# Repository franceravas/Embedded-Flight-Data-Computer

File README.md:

# README.md

Collect inertial and GPS data, timestamp it, and save it to a microSD card for later analysis.

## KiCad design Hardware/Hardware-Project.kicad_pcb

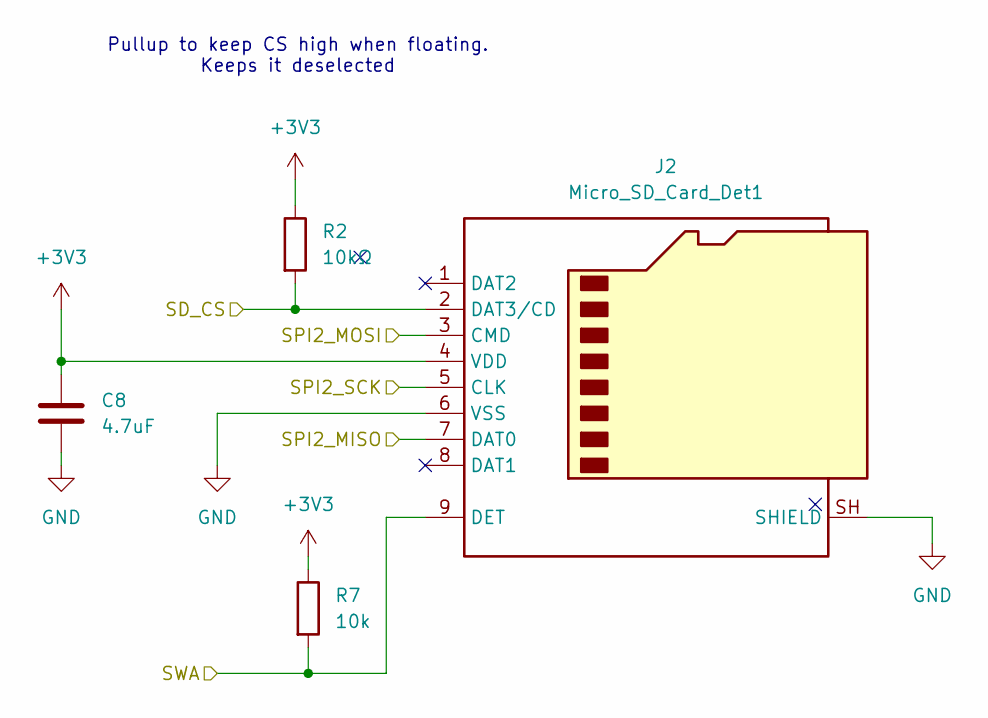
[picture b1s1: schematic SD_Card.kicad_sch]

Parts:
C8: 4.7uF; C_1206_3216Metric_Pad1.33x1.80mm_HandSolder
J2: Micro_SD_Card_Det1; microSD_HC_Hirose_DM3AT-SF-PEJM5
R2: 10kΩ; R_1206_3216Metric_Pad1.30x1.75mm_HandSolder
R7: 10k; R_1206_3216Metric_Pad1.30x1.75mm_HandSolder

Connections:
+3V3: C8.1, J2.4 (VDD), R2.1, R7.1; also elsewhere on the board
/SD_Card/SD_CS: J2.2 (DAT3/CD), R2.2; also elsewhere on the board
/SD_Card/SPI2_MISO: J2.7 (DAT0); also elsewhere on the board
/SD_Card/SPI2_MOSI: J2.3 (CMD); also elsewhere on the board
/SD_Card/SPI2_SCK: J2.5 (CLK); also elsewhere on the board
/SD_Card/SWA: J2.9 (DET), R7.2; also elsewhere on the board
GND: C8.2, J2.6 (VSS), J2.SH (SHIELD); also elsewhere on the board

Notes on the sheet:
Pullup to keep CS high when floating. Keeps it deselected

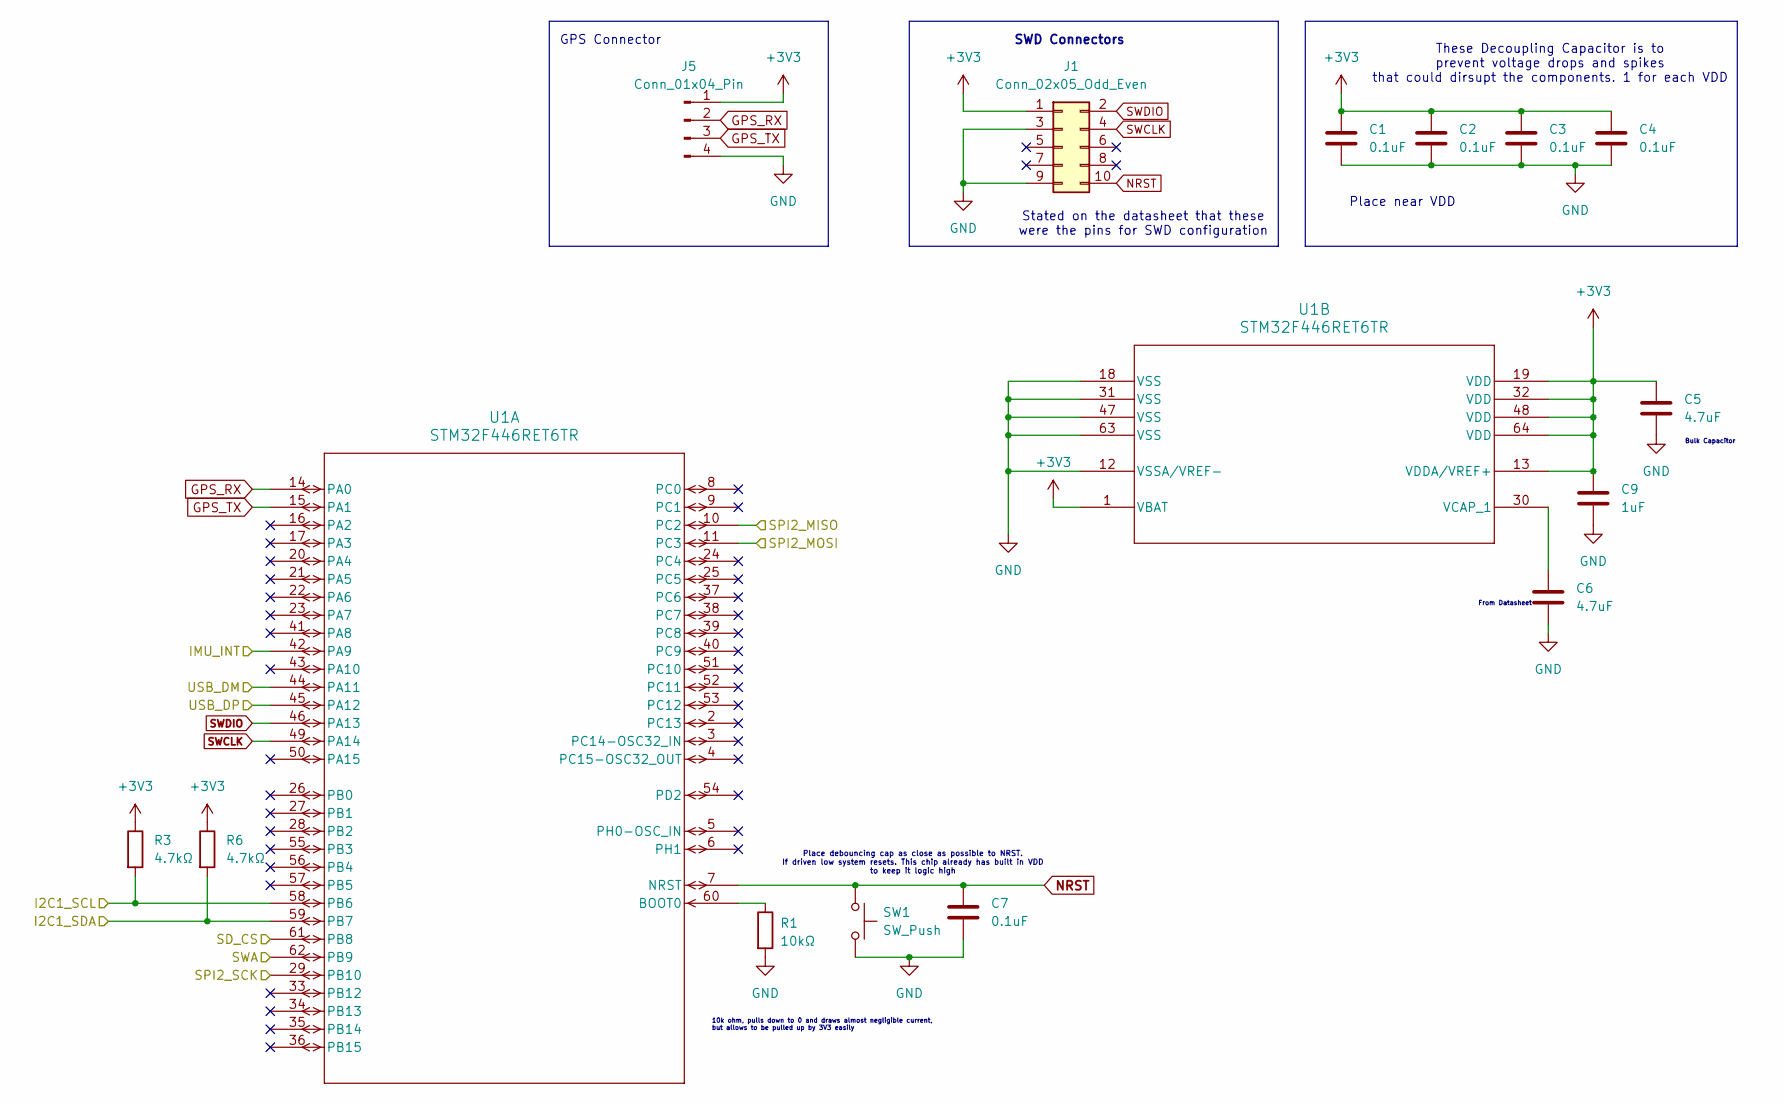
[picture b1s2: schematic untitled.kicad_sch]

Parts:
C1, C2, C3, C4, C7: 0.1uF; C_0603_1608Metric_Pad1.08x0.95mm_HandSolder
C5, C6: 4.7uF; C_1206_3216Metric_Pad1.33x1.80mm_HandSolder
C9: 1uF; C_1206_3216Metric_Pad1.33x1.80mm_HandSolder
J1: Conn_02x05_Odd_Even; PinSocket_2x05_P1.27mm_Vertical
J5: Conn_01x04_Pin; PinSocket_1x04_P2.54mm_Vertical
R1: 10kΩ; R_1206_3216Metric_Pad1.30x1.75mm_HandSolder
R3, R6: 4.7kΩ; R_0603_1608Metric_Pad0.98x0.95mm_HandSolder
SW1: SW_Push; SW_Push_1P1T_NO_CK_KMR2
U1: STM32F446RET6TR; STM32446RET6TR

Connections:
+3V3: C1.1, C2.1, C3.1, C4.1, C5.1, C9.1, J1.1, J5.1, R3.1, R6.1, U1.1 (VBAT), U1.13 (VDDA/VREF+), U1.19 (VDD), U1.32 (VDD), U1.48 (VDD), U1.64 (VDD); also elsewhere on the board
/IMU/I2C1_SCL: R3.2, U1.58 (PB6); also elsewhere on the board
/IMU/I2C1_SDA: R6.2, U1.59 (PB7); also elsewhere on the board
/IMU/IMU_INT: U1.42 (PA9); also elsewhere on the board
/SD_Card/SD_CS: U1.61 (PB8); also elsewhere on the board
/SD_Card/SPI2_MISO: U1.10 (PC2); also elsewhere on the board
/SD_Card/SPI2_MOSI: U1.11 (PC3); also elsewhere on the board
/SD_Card/SPI2_SCK: U1.29 (PB10); also elsewhere on the board
/SD_Card/SWA: U1.62 (PB9); also elsewhere on the board
/STM32F446RE LQFP64/USB_DM: U1.44 (PA11); also elsewhere on the board
/STM32F446RE LQFP64/USB_DP: U1.45 (PA12); also elsewhere on the board
GND: C1.2, C2.2, C3.2, C4.2, C5.2, C6.2, C7.2, C9.2, J1.3, J1.9, J5.4, R1.2, SW1.2, U1.12 (VSSA/VREF-), U1.18 (VSS), U1.31 (VSS), U1.47 (VSS), U1.63 (VSS); also elsewhere on the board
GPS_RX: J5.2, U1.14 (PA0)
GPS_TX: J5.3, U1.15 (PA1)
NRST: C7.1, J1.10, SW1.1, U1.7 (NRST)
unnamed: R1.1, U1.60 (BOOT0)
unnamed: C6.1, U1.30 (VCAP_1)
SWCLK: J1.4, U1.49 (PA14)
SWDIO: J1.2, U1.46 (PA13)

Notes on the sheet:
Place near VDD
10k ohm, pulls down to 0 and draws almost negligible current, but allows to be pulled up by 3V3 easily
Place debouncing cap as close as possible to NRST. If driven low system resets. This chip already has built in VDD to keep it logic high
Stated on the datasheet that these were the pins for SWD configuration
From Datasheet
GPS Connector
SWD Connectors
Bulk Capacitor
These Decoupling Capacitor is to prevent voltage drops and spikes that could dirsupt the components. 1 for each VDD

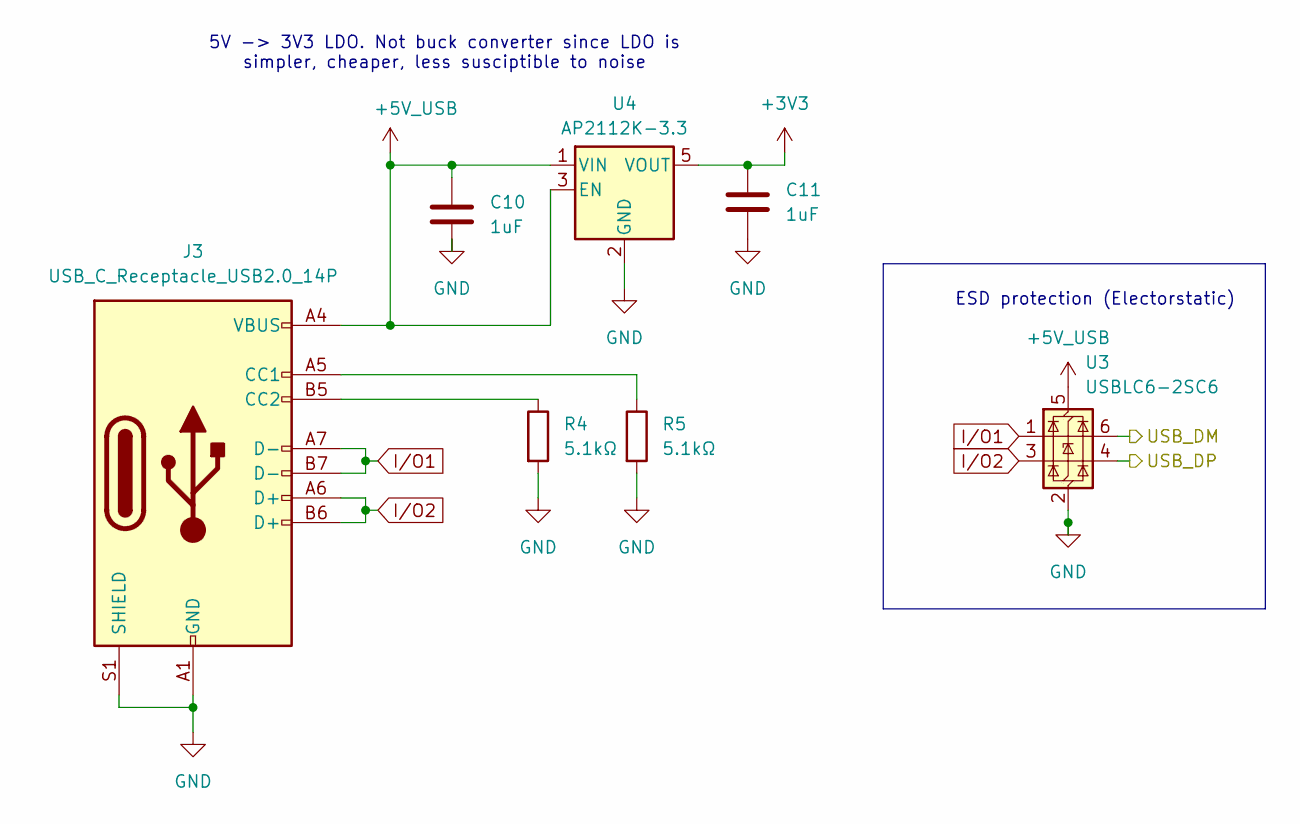
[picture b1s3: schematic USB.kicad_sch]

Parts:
C10, C11: 1uF; C_1206_3216Metric_Pad1.33x1.80mm_HandSolder
J3: USB_C_Receptacle_USB2.0_14P; USB_C_Receptacle_HRO_TYPE-C-31-M-12
R4, R5: 5.1kΩ; R_0603_1608Metric_Pad0.98x0.95mm_HandSolder
U3: USBLC6-2SC6; SOT-23-6
U4: AP2112K-3.3; SOT-23-5

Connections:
+3V3: C11.1, U4.5 (VOUT); also elsewhere on the board
+5V_USB: C10.1, J3.A4 (VBUS), J3.A9 (VBUS), J3.B4 (VBUS), J3.B9 (VBUS), U3.5 (VBUS), U4.1 (VIN), U4.3 (EN)
/STM32F446RE LQFP64/USB_DM: U3.6 (I/O1); also elsewhere on the board
/STM32F446RE LQFP64/USB_DP: U3.4 (I/O2); also elsewhere on the board
GND: C10.2, C11.2, J3.A1 (GND), J3.A12 (GND), J3.B1 (GND), J3.B12 (GND), J3.S1 (SHIELD), R4.2, R5.2, U3.2 (GND), U4.2 (GND); also elsewhere on the board
I/O1: J3.A7 (D-), J3.B7 (D-), U3.1 (I/O1)
I/O2: J3.A6 (D+), J3.B6 (D+), U3.3 (I/O2)
unnamed: J3.A5 (CC1), R5.1
unnamed: J3.B5 (CC2), R4.1

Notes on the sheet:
5V -> 3V3 LDO. Not buck converter since LDO is simpler, cheaper, less susciptible to noise
ESD protection (Electorstatic)

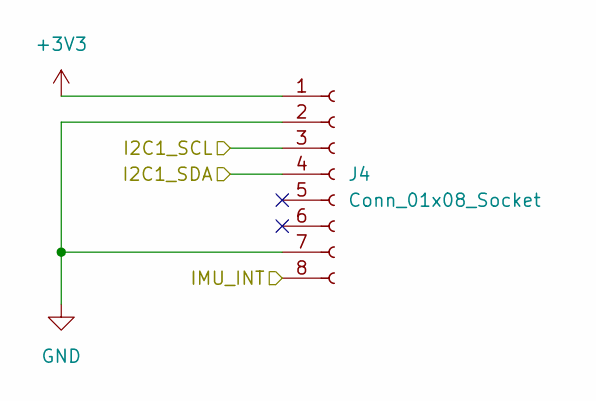
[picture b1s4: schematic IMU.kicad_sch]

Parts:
J4: Conn_01x08_Socket; PinSocket_1x08_P2.54mm_Vertical

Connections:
+3V3: J4.1; also elsewhere on the board
/IMU/I2C1_SCL: J4.3; also elsewhere on the board
/IMU/I2C1_SDA: J4.4; also elsewhere on the board
/IMU/IMU_INT: J4.8; also elsewhere on the board
GND: J4.2, J4.7; also elsewhere on the board

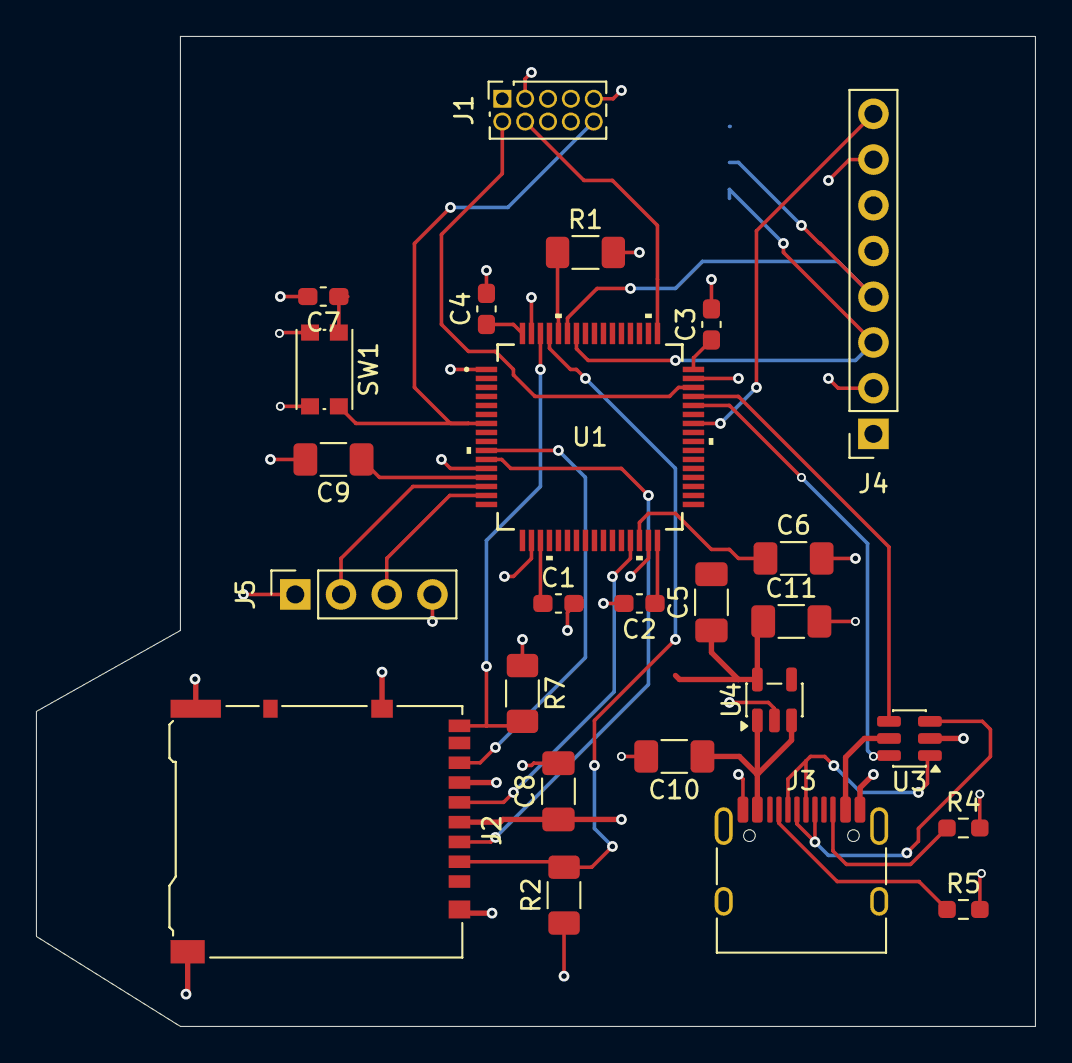
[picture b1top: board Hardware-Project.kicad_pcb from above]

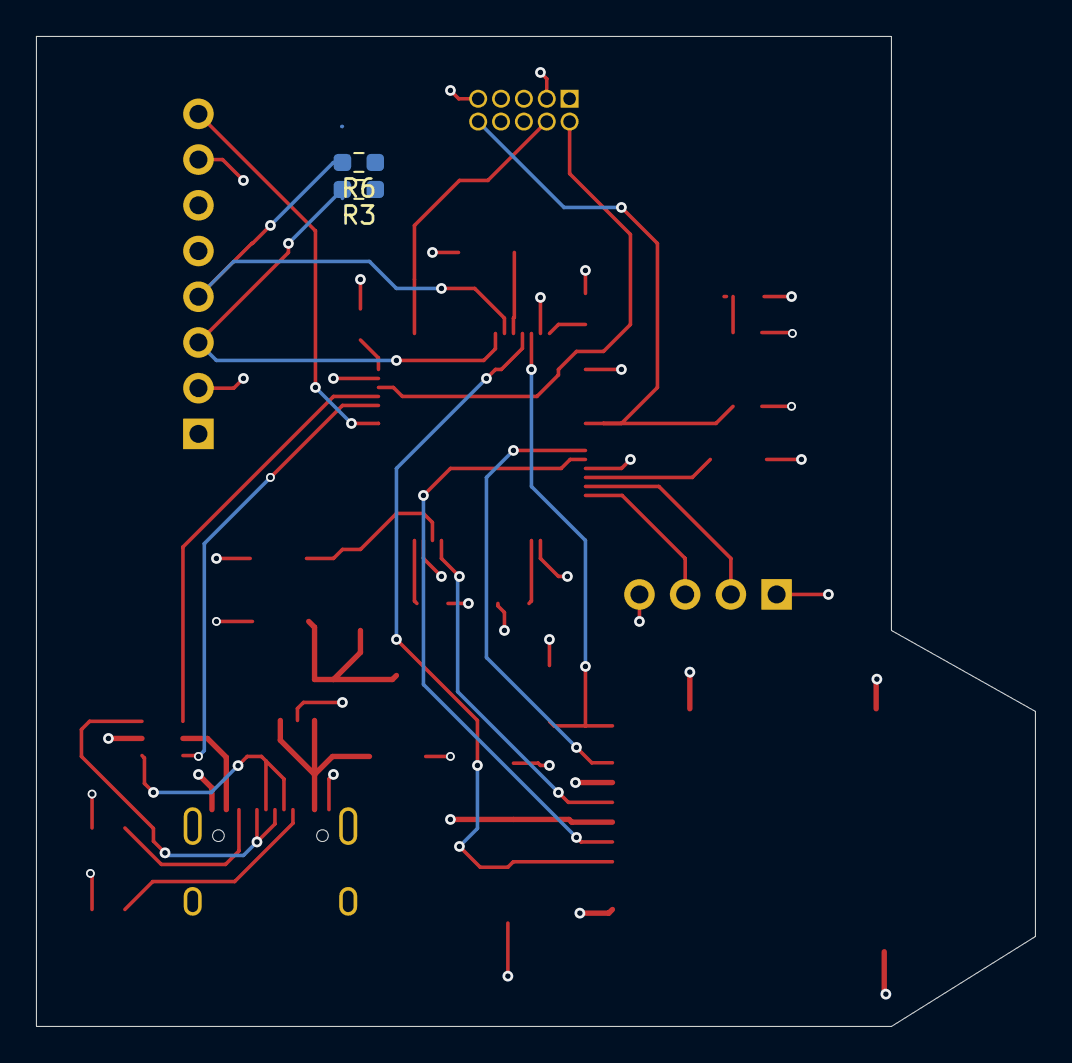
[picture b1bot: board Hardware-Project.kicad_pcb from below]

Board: 4 copper layers, 55.5 x 55.0 mm, 27 parts (2 on the bottom side), 24 nets.
